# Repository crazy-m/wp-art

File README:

ART - Automatska Regulacija Temperature

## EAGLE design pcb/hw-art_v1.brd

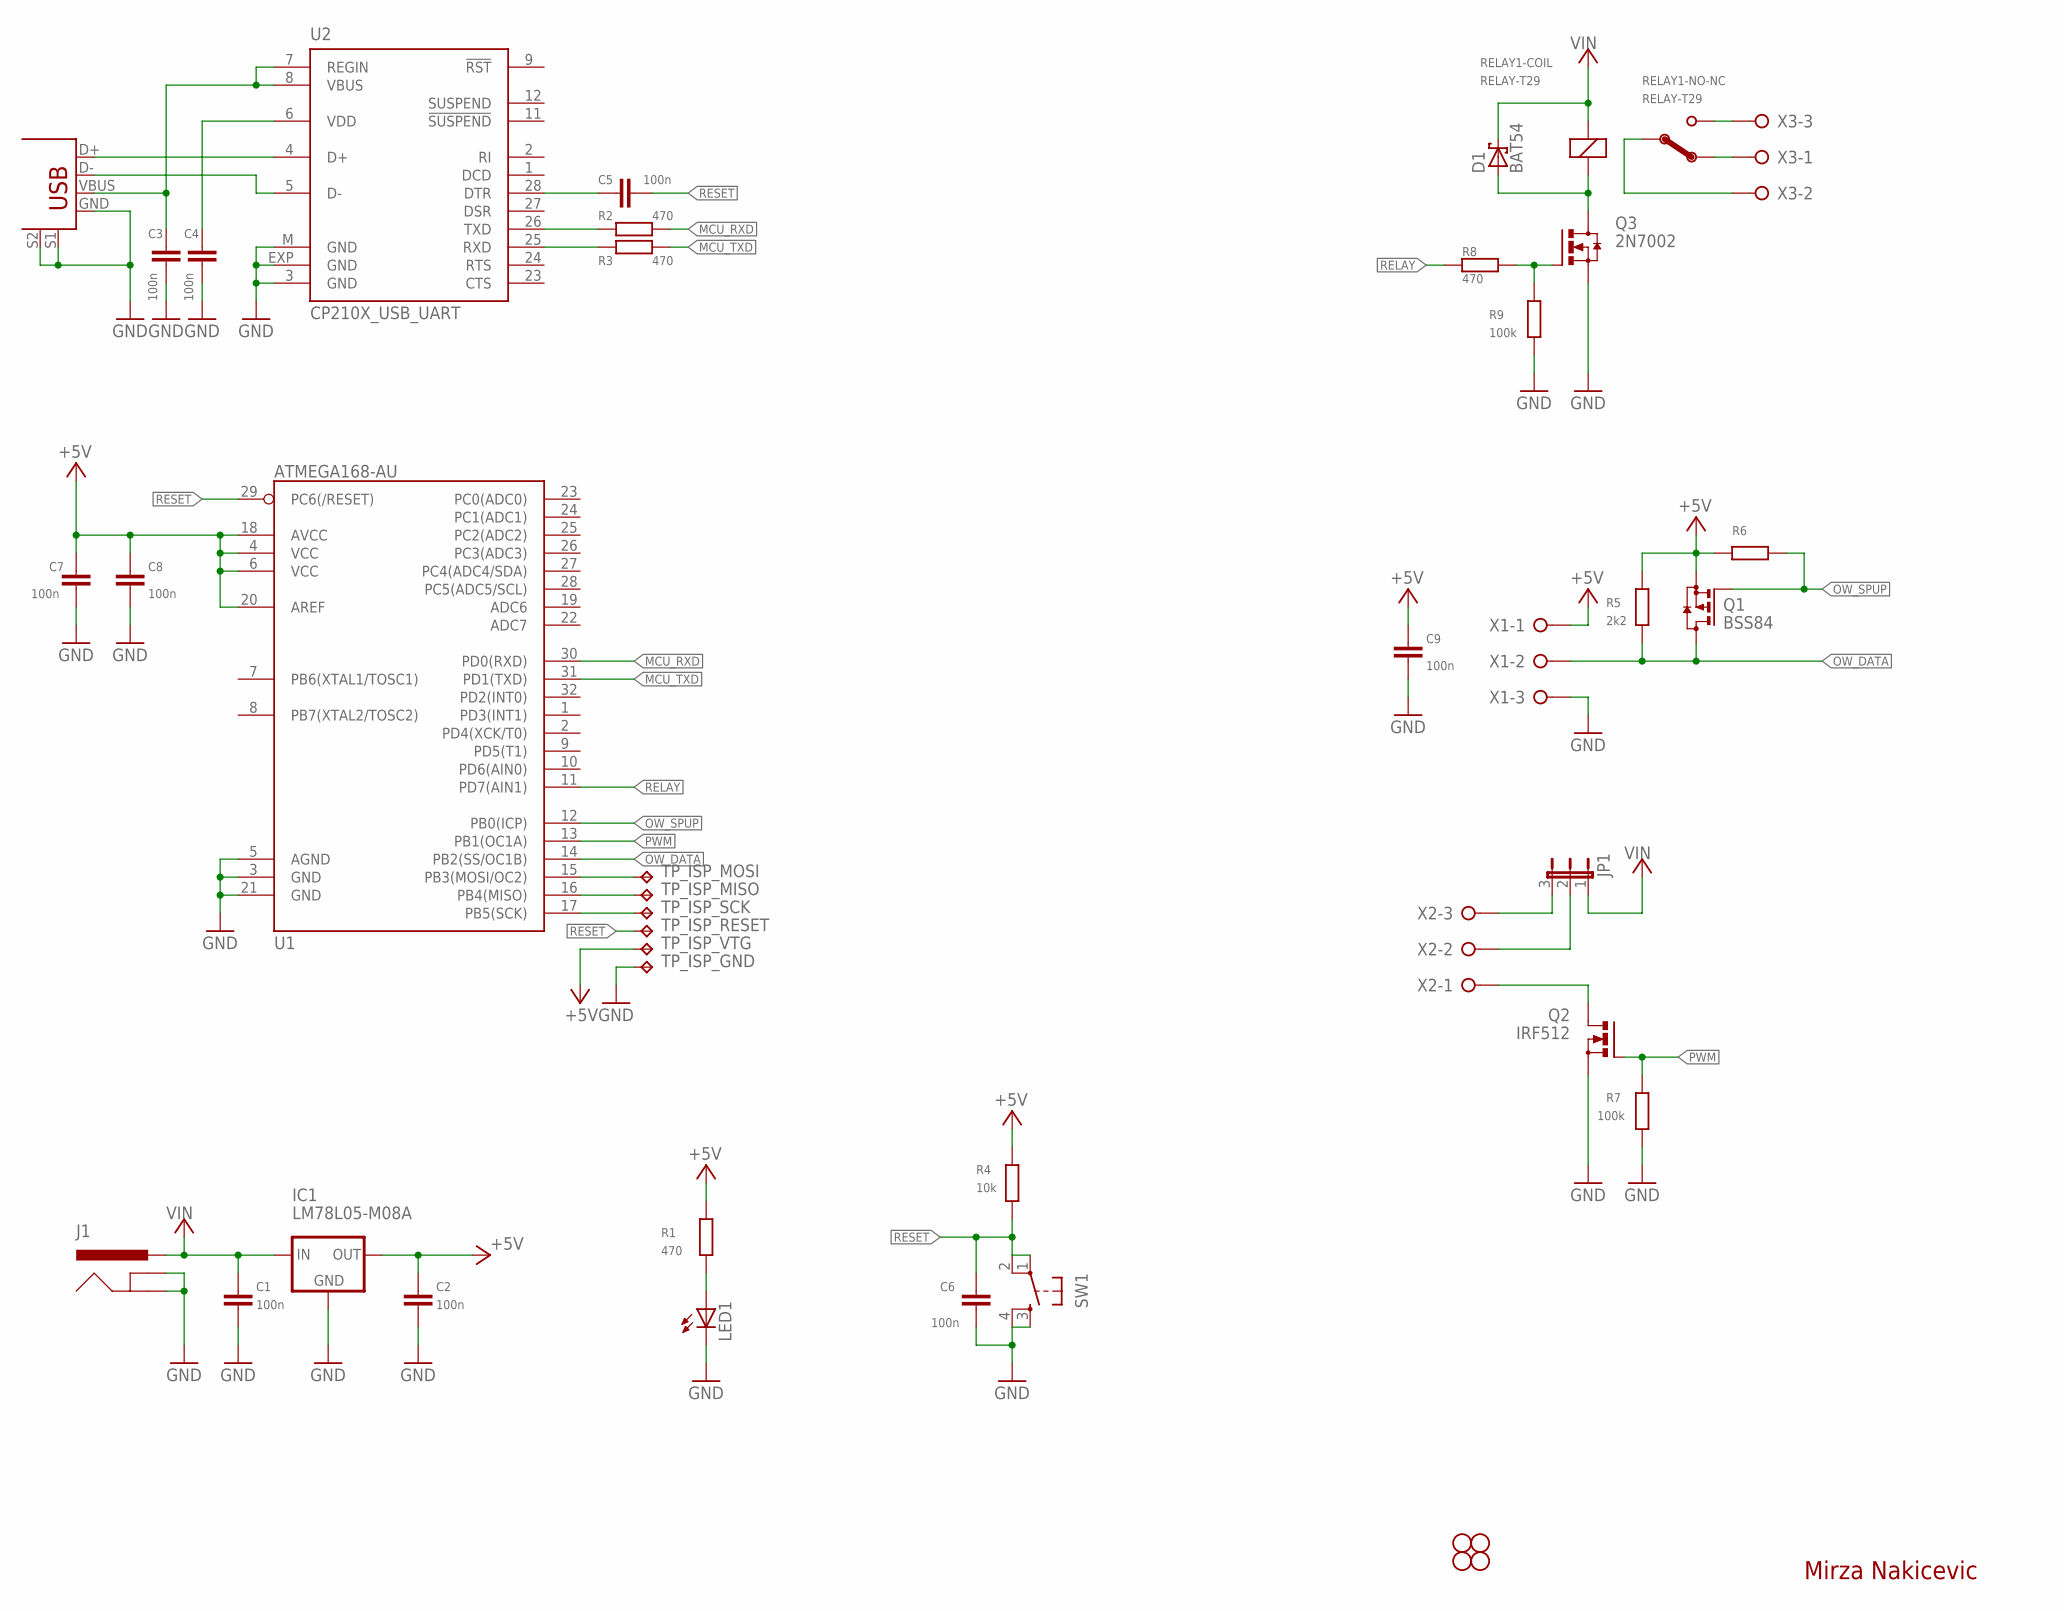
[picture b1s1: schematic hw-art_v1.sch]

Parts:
C1, C2, C3, C4, C5, C6, C7, C8, C9: 100n; C0603
D1: BAT54; SOT23
IC1: LM78L05-M08A; SO-08
J1: DCJACK-05537; 4UCON-05537
J2: USB+SHIELD; USB-B-PTH
JP1: JP2E; JP2
LED1: LEDCHIP-LED0805; CHIP-LED0805
Q1: BSS84; SOT23
Q2: IRF512; TO220BV
Q3: 2N7002; SOT-23
R1, R2, R3, R8: 470; R0603
R4: 10k; R0603
R5: 2k2; R0603
R6: R-0603; R0603
R7, R9: 100k; R0603
RELAY1: RELAY-T29; FINDER_T29
SW1: TAC_SWITCHPTH; TACTILE-PTH
TP_ISP_GND: TPTP08R; TP08R
TP_ISP_MISO: TPTP08R; TP08R
TP_ISP_MOSI: TPTP08R; TP08R
TP_ISP_RESET: TPTP08R; TP08R
TP_ISP_SCK: TPTP08R; TP08R
TP_ISP_VTG: TPTP08R; TP08R
U1: ATMEGA168-AU; TQFP32-08
U2: CP210X_USB_UART; MLP28
U$1, U$2, U$3, U$4: STAND-OFF
X1, X2, X3: W237-03P; W237-133

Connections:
!RESET: C5.2, C6.2, R4.1, SW1.1, SW1.2, TP_ISP_RESET.TP, U1.29 (PC6(/RESET))
+5V: C2.1, C7.1, C8.1, C9.1, IC1.1 (OUT), Q1.2 (S), R1.2, R4.2, R5.2, R6.1, TP_ISP_VTG.TP, U1.4 (VCC), U1.6 (VCC), U1.18 (AVCC), U1.20 (AREF), X1.1
GND: C1.2, C2.2, C3.2, C4.2, C6.1, C7.2, C8.2, C9.2, IC1.2 (GND), IC1.3 (GND), IC1.6 (GND), IC1.7 (GND), J1.2 (GND), J1.3 (GNDBREAK), J2.GND, J2.S1, J2.S2, LED1.C, Q2.S, Q3.2 (S), R7.2, R9.1, SW1.3, SW1.4, TP_ISP_GND.TP, U1.3 (GND), U1.5 (AGND), U1.21 (GND), U2.3 (GND), U2.EXP (GND), U2.M (GND), X1.3
MCU_RXD: R2.2, U1.30 (PD0(RXD))
MCU_TXD: R3.2, U1.31 (PD1(TXD))
unnamed: J2.D+, U2.4 (D+)
unnamed: J2.D-, U2.5 (D-)
unnamed: C4.1, U2.6 (VDD)
unnamed: R2.1, U2.26 (TXD)
unnamed: R3.1, U2.25 (RXD)
unnamed: C5.1, U2.28 (DTR)
unnamed: RELAY1.NC, X3.1
unnamed: Q2.D, X2.1
unnamed: JP1.3, X2.3
unnamed: LED1.A, R1.1
unnamed: JP1.2, X2.2
unnamed: TP_ISP_MOSI.TP, U1.15 (PB3(MOSI/OC2))
unnamed: TP_ISP_MISO.TP, U1.16 (PB4(MISO))
unnamed: TP_ISP_SCK.TP, U1.17 (PB5(SCK))
unnamed: RELAY1.NO, X3.3
unnamed: D1.1 (A), Q3.3 (D), RELAY1.-
unnamed: RELAY1.COM, X3.2
unnamed: Q3.1 (G), R8.1, R9.2
OW_DATA: Q1.3 (D), R5.1, U1.14 (PB2(SS/OC1B)), X1.2
OW_SPUP: Q1.1 (G), R6.2, U1.12 (PB0(ICP))
PWM: Q2.G, R7.1, U1.13 (PB1(OC1A))
RELAY: R8.2, U1.11 (PD7(AIN1))
VBUS: C3.1, J2.VBUS, U2.7 (REGIN), U2.8 (VBUS)
VIN: C1.1, D1.3 (C), IC1.8 (IN), J1.1 (PWR), JP1.1, RELAY1.+

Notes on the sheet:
Mirza Nakicevic

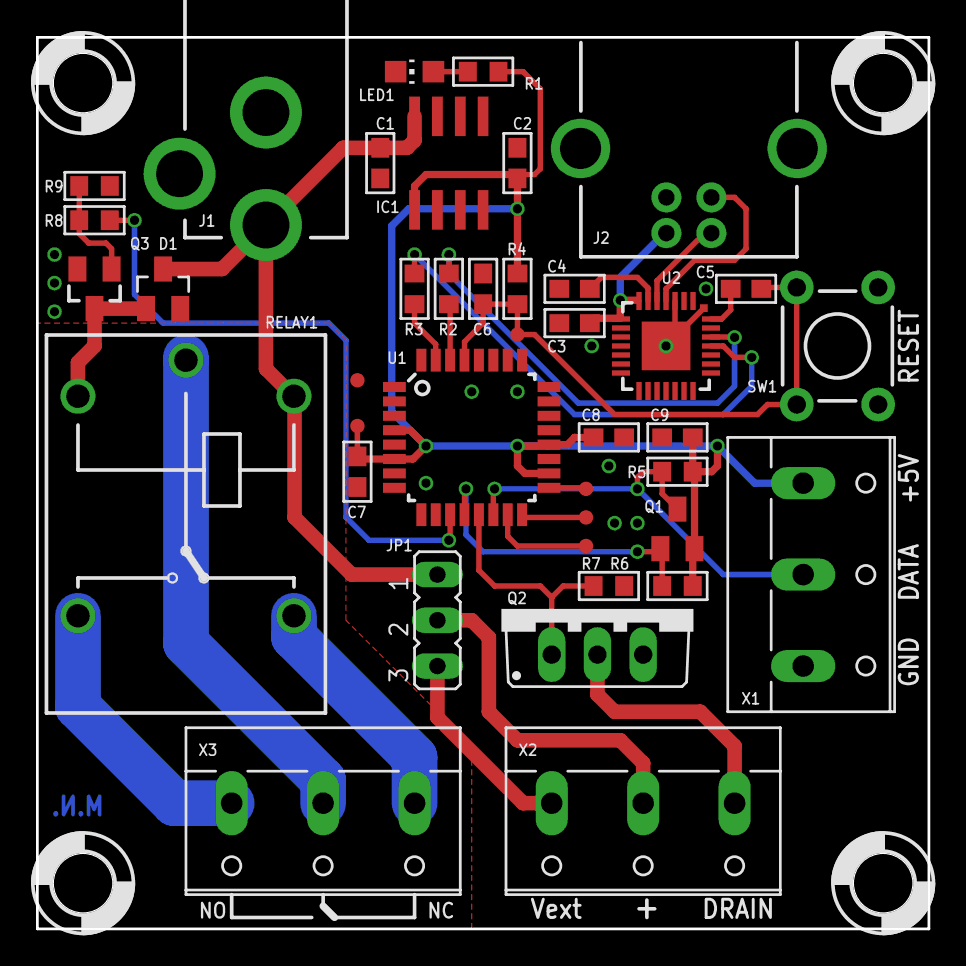
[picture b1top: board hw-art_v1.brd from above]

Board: 2 copper layers, 49.5 x 49.5 mm, 44 parts (0 on the bottom side), 29 nets.

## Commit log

2012-02-15 licence header in files changed, added pcb files for hardware, Cadsoft Eagle 6 format
2012-02-17 added art.pde in pcb dir

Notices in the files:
parts and their libraries:
SparkFun: Licensing: CC v3.0 Share-Alike You are welcome to use this library for commercial purposes.
